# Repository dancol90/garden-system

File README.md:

garden-system
=============

This sketches depends on some library:

- LightPCD8544 https://github.com/dancol90/LightPCD8544
- MenuLib https://github.com/dancol90/MenuLib
- RF24 https://github.com/maniacbug/RF24

- Arduino 1.6.2's EEPROM library.

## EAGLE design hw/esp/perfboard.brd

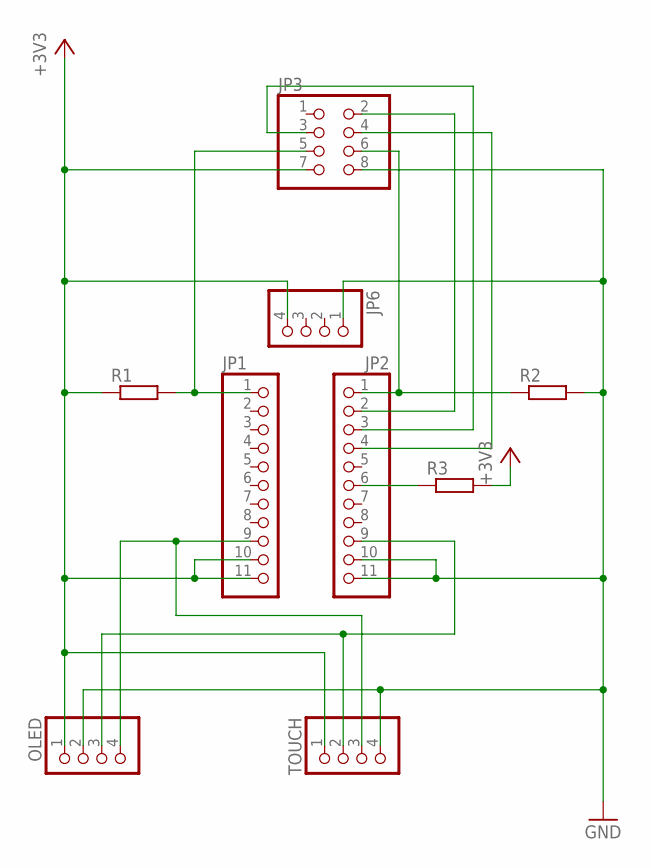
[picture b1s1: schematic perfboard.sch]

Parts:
JP1, JP2: PINHD-1X11; 1X11
JP3: PINHD-2X4; 2X04
JP6: PINHD-1X4; 1X04
OLED: PINHD-1X4; 1X04
R1, R2, R3: R-EU_0207/7; 0207/7
TOUCH: PINHD-1X4; 1X04

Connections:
+3V3: JP1.10, JP1.11, JP3.7, JP6.4, OLED.1, R1.1, R3.2, TOUCH.1
GND: JP2.10, JP2.11, JP3.8, JP6.1, OLED.2, R2.2, TOUCH.4
unnamed: JP2.2, JP3.2
unnamed: JP2.3, JP3.3
unnamed: JP2.4, JP3.4
unnamed: JP1.1, JP3.5, R1.2
unnamed: JP1.9, OLED.4, TOUCH.3
unnamed: JP2.9, OLED.3, TOUCH.2
unnamed: JP2.6, R3.1
unnamed: JP2.1, JP3.6, R2.1

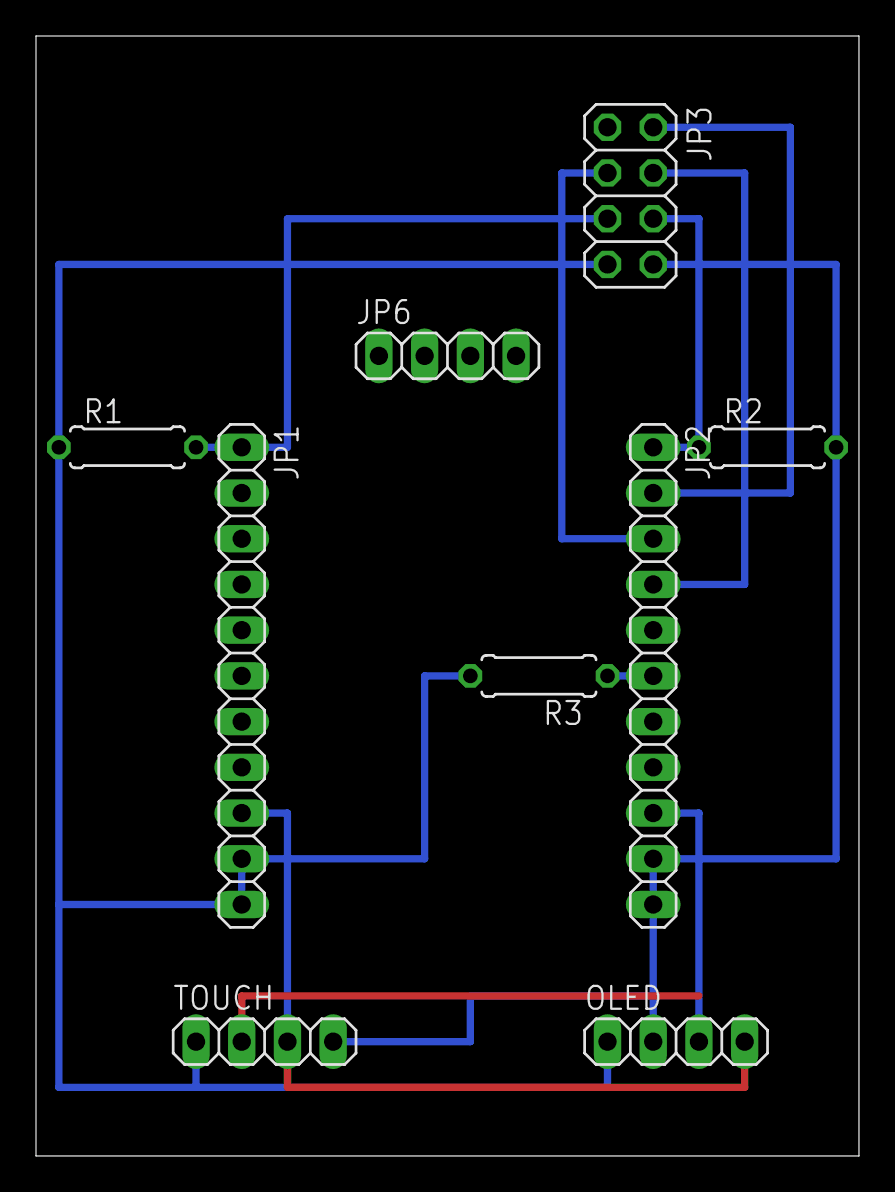
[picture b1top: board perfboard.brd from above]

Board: 2 copper layers, 45.7 x 62.2 mm, 9 parts (0 on the bottom side), 10 nets.

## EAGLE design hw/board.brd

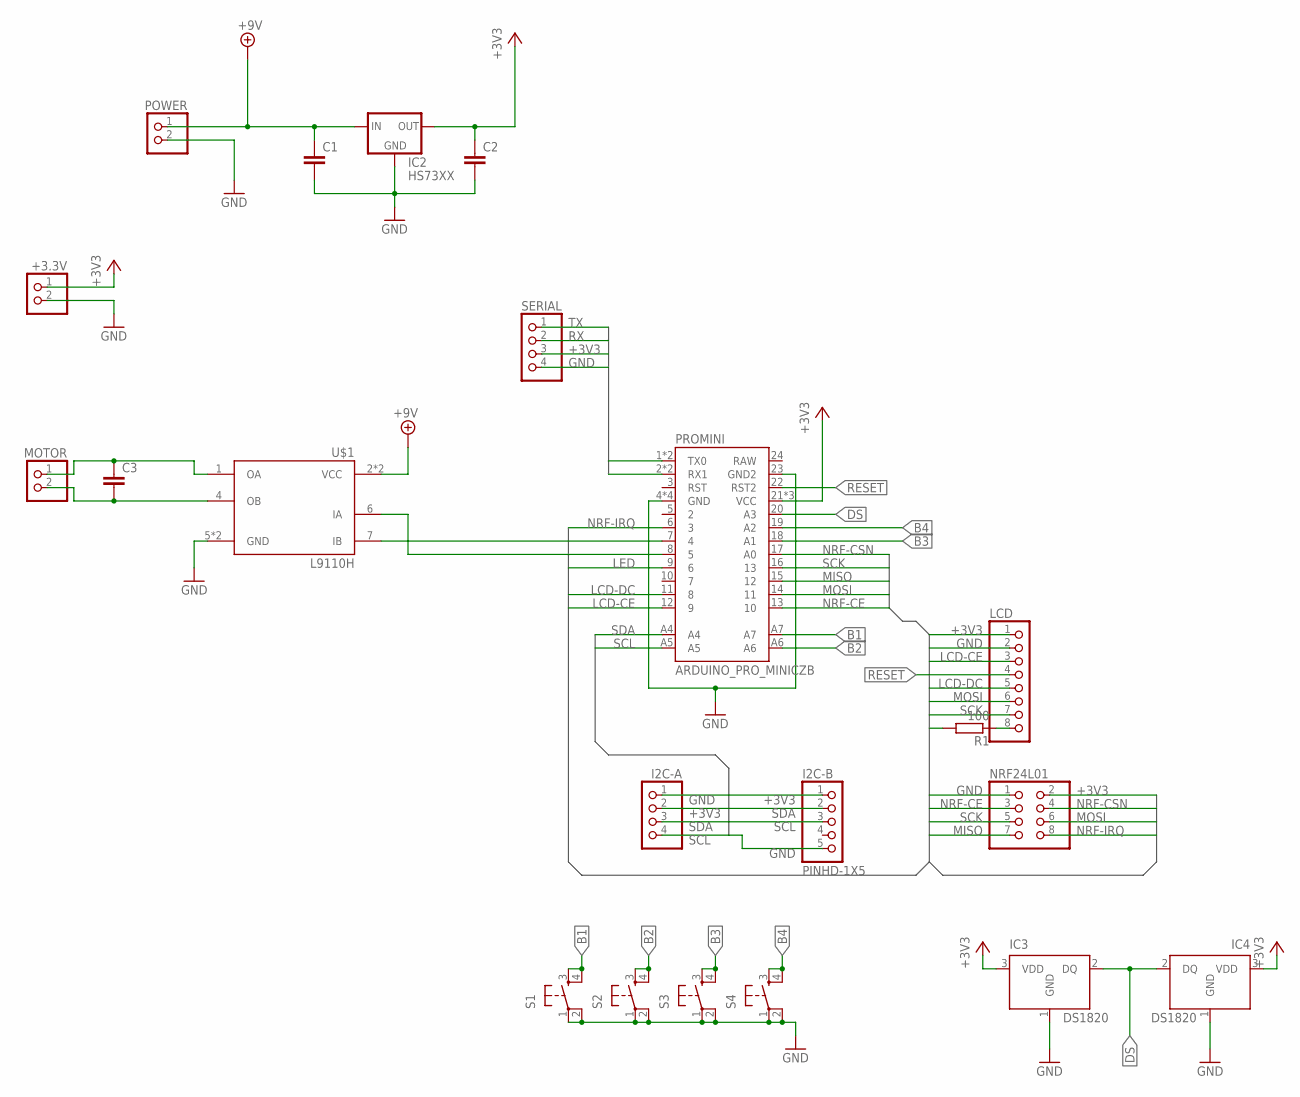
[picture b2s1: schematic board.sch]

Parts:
+3.3V: PINHD-1X2; 1X02
C1, C2, C3: C-EU025-024X044; C025-024X044
I2C-A: PINHD-1X4; 1X04
I2C-B: PINHD-1X5; 1X05
IC2: HS73XX; TO92
IC3, IC4: DS1820; TO-92
LCD: PINHD-1X8; 1X08
MOTOR: PINHD-1X2; 1X02
NRF24L01: PINHD-2X4; 2X04
POWER: PINHD-1X2; 1X02
PROMINI: ARDUINO_PRO_MINICZB; PRO_MINI_2
R1: 100; 0204/7
S1, S2, S3, S4: TAC_SWITCHPTH; TACTILE-PTH
SERIAL: PINHD-1X4; 1X04
U$1: L9110H; DIL08

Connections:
1Y: C3.1, MOTOR.1, U$1.1 (OA)
2Y: C3.2, MOTOR.2, U$1.4 (OB)
+3V3: +3.3V.1, C2.1, I2C-A.2, I2C-B.1, IC2.3 (OUT), IC3.3 (VDD), IC4.3 (VDD), LCD.1, NRF24L01.2, PROMINI.21 (VCC), PROMINI.V (VCC), PROMINI.VCC, SERIAL.3
+9V: C1.1, IC2.2 (IN), POWER.1, U$1.2 (VCC), U$1.3 (VCC)
B1: PROMINI.A7, S1.3, S1.4
B2: PROMINI.A6, S2.3, S2.4
B3: PROMINI.18 (A1), S3.3, S3.4
B4: PROMINI.19 (A2), S4.3, S4.4
DS: IC3.2 (DQ), IC4.2 (DQ), PROMINI.20 (A3)
GND: +3.3V.2, C1.2, C2.2, I2C-A.1, I2C-B.5, IC2.1 (GND), IC3.1 (GND), IC4.1 (GND), LCD.2, NRF24L01.1, POWER.2, PROMINI.4 (GND), PROMINI.23 (GND2), PROMINI.BLK (GND), PROMINI.G (GND), PROMINI.GND, S1.1, S1.2, S2.1, S2.2, S3.1, S3.2, S4.1, S4.2, SERIAL.4, U$1.5 (GND), U$1.8 (GND)
LCD-CE: LCD.3, PROMINI.12 (9)
LCD-DC: LCD.5, PROMINI.11 (8)
LED: PROMINI.9 (6), R1.2
LED-LCD: LCD.8, R1.1
MISO: NRF24L01.7, PROMINI.15 (12)
MOSI: LCD.6, NRF24L01.6, PROMINI.14 (11)
unnamed: PROMINI.8 (5), U$1.6 (IA)
unnamed: PROMINI.7 (4), U$1.7 (IB)
NRF-CE: NRF24L01.3, PROMINI.13 (10)
NRF-CSN: NRF24L01.4, PROMINI.17 (A0)
NRF-IRQ: NRF24L01.8, PROMINI.6 (3)
RESET: LCD.4, PROMINI.22 (RST2)
RX: PROMINI.2 (RX1), PROMINI.RXI (RX1), SERIAL.2
SCK: LCD.7, NRF24L01.5, PROMINI.16 (13)
SCL: I2C-A.4, I2C-B.3, PROMINI.A5
SDA: I2C-A.3, I2C-B.2, PROMINI.A4
TX: PROMINI.1 (TX0), PROMINI.TXO (TX0), SERIAL.1

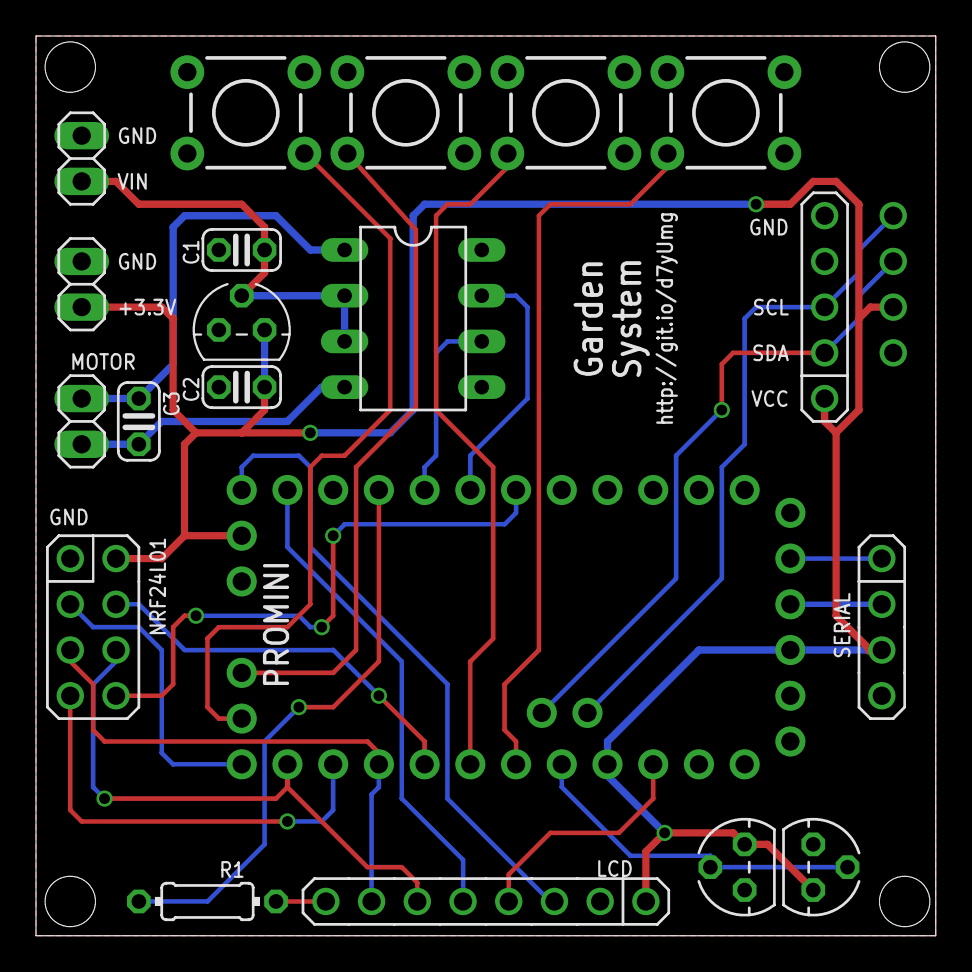
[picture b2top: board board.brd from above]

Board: 2 copper layers, 50.0 x 50.0 mm, 21 parts (1 on the bottom side), 27 nets.

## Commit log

2014-07-13 Added hardware files
2014-07-14 PCB fixes
2014-07-16 Changes to the board
2014-10-19 Added firmware
2015-02-28 Almost rewritten receiver firmware. Arduino sleep missing.
2015-03-14 First UI draft.
2015-03-14 Divided source in modules
2015-03-15 More modularity
2015-03-16 More work
2015-03-16 Updated read
2015-03-24 Added license headers
2015-03-29 Added dynamic graphic indicator on home screen
2015-03-29 Added new menu item type, TimeSelector, and its relative drawing routine, following new additions in MenuLib.
2015-03-30 TimerSelector now works
2015-03-30 Refined homescreen drawing
2015-03-30 Fixed swapped MISO/MOSI in pcb design. -_-
2015-03-30 Added dynamic text to Jobs list to reflect jobs intervals
2015-04-01 Small changes, working on the jobs editing
2015-04-01 There's no enough free RAM to keep 20 jobs. Have to move to EEPROM.
2015-04-01 EEPROM lookup for jobs' data now works
2015-04-01 Refinements and new stuff
2015-04-02 Moved settings-related stuff away from ApplicationState to a dedicated struct
2015-04-02 Redraw home screen every 300ms or on key-press only.
2015-04-02 Add: Delete and disable job. Add: eeprom formatting on request. Add: Save settings to eeprom on confirmation
2015-04-02 Add: time can be set in Settings
2015-04-02 Add: "Add job" now hides if there are no space for a new one. Fix: Little things
2015-04-03 Fixes and missing license header
2015-04-03 Changed Job editor behaviour
    Now autosaves on start/end time change
2015-04-03 Add: schedule management
    Checks every minute if there’s job to be done.
2015-04-03 Fixed schedule
2015-04-03 Some improvements
2015-04-04 Added backlight timeout
2015-04-09 Working on rf communications.
2015-04-09 Debug prints in receiver
2015-04-10 Switched to ACK payload
2015-04-10 Switched receiver to ACK payload
    But it doesn’t sleep at all.
2015-04-11 Fixed receiver
    For some reason sleep wasn’t working anymore. Changed wdt code to
    better one.
2015-04-12 Small fix
2015-04-12 Fixed forced state
2015-04-12 Received state is actuated through the h-bridge.
    Also replaced delay() with sleep mode.
2015-04-12 Code refactoring
    Added lots of comments, but not all yet
2015-05-06 Added visuals for rf communications
2015-05-06 First support for ESP8266
2015-05-06 Changed timings in actuators
2015-05-12 Fixed configuration includes
2015-05-12 Added key repetition on hold for buttons
2015-05-26 Moving to ESP8266
    Replaced buttons with MPR121 touch and Nokia lcd with SSD1306 OLED
2015-06-01 Small fixes
2015-06-20 Changed to Makefile system
2015-06-21 Fixed all compile problems
2015-06-26 First WiFi things
2015-07-20 esp8266 perfboard schematics
2015-07-20 Updated Makefile to new core's staging release
2015-07-20 Re-enabling rf comms and fixing pin defs
2015-07-20 Added menu for WiFi connection and passphrase
2015-07-21 Add basic retriggering to input
2015-07-21 Added and moved WiFi related function to proper files
2015-07-21 Draw WiFi signal bars on screen
2015-07-21 NTP clock sync
2015-07-21 Code refactoring
2017-04-22 Moved to PlatformIO
2020-06-27 Add libs as submodules
2020-06-27 Fix platform
2020-06-27 Readd support for GPIO inputs
2020-06-27 Defer homescreen initialization to avoid bootloop
2020-06-27 Make I2C pins configurable
2020-06-27 Update LightLCD
2020-06-27 Fix pins
2020-06-27 Remove some global variables
2020-06-27 Add exception stack decoder filter

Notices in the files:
parts and their libraries:
SparkFun-Electromechanical: Licensing: CC v3.0 Share-Alike You are welcome to use this library for commercial purposes.
